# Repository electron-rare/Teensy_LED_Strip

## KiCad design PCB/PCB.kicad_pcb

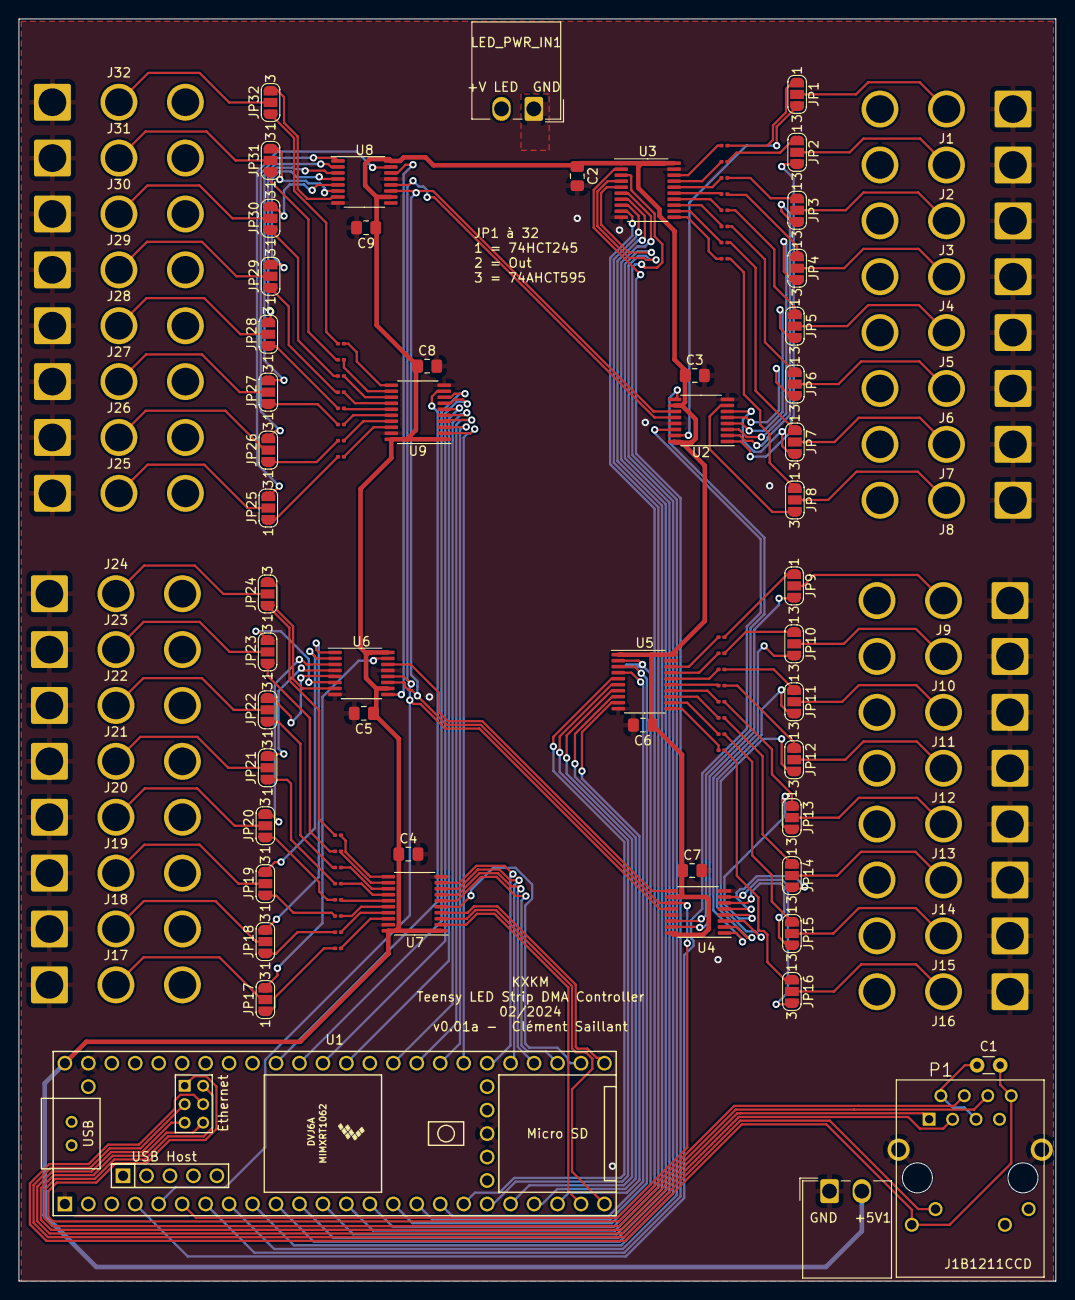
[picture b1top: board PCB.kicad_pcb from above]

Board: 2 copper layers, 112.3 x 136.7 mm, 117 parts (0 on the bottom side), 176 nets.

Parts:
+5V1: Screw_Terminal_01x02; Wago_734-162_1x02_P3.50mm_Horizontal
C1: 0.1uF; C_Disc_D3.0mm_W1.6mm_P2.50mm
C2, C3, C4, C5, C6, C7, C8, C9: 100nf; C_0805_2012Metric_Pad1.18x1.45mm_HandSolder
J1, J2, J3, J4, J5, J6, J7, J8, J9, J10, J11, J12, J13, J14, J15, J16, J17, J18, J19, J20, J21, J22, J23, J24, J25, J26, J27, J28, J29, J30, J31, J32: Conn_01x03_Pin; SolderWire-2.5sqmm_1x03_P7.2mm_D2.4mm_OD3.6mm
JP1, JP2, JP3, JP4, JP5, JP6, JP7, JP8, JP9, JP10, JP11, JP12, JP13, JP14, JP15, JP16, JP17, JP18, JP19, JP20, JP21, JP22, JP23, JP24, JP25, JP26, JP27, JP28, JP29, JP30, JP31, JP32: SolderJumper_3_Open; SolderJumper-3_P1.3mm_Open_RoundedPad1.0x1.5mm_NumberLabels
LED_PWR_IN1: Screw_Terminal_01x02; Wago_734-162_1x02_P3.50mm_Horizontal
P1: J1B1211CCD
R1, R2, R3, R4, R5, R6, R7, R8, R9, R10, R11, R12, R13, R14, R15, R16, R17, R18, R19, R20, R21, R22, R23, R24, R25, R26, R27, R28, R29, R30, R31, R32: 100R; R_0201_0603Metric
U1: Teensy4.1; Teensy41
U2, U4, U6, U8: 74AHCT595; TSSOP-16_4.4x5mm_P0.65mm
U3, U5, U7, U9: 74HCT245; TSSOP-20_4.4x6.5mm_P0.65mm

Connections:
+5V: +5V1.2, C2.1, C3.1, C4.1, C5.1, C6.1, C7.1, C8.1, C9.1, U1.48 (VIN), U2.10 (~SRCLR), U2.16 (VCC), U3.1 (A->B), U3.20 (VCC), U4.10 (~SRCLR), U4.16 (VCC), U5.1 (A->B), U5.20 (VCC), U6.10 (~SRCLR), U6.16 (VCC), U7.1 (A->B), U7.20 (VCC), U8.10 (~SRCLR), U8.16 (VCC), U9.1 (A->B), U9.20 (VCC)
+12V: J1.3, J2.3, J3.3, J4.3, J5.3, J6.3, J7.3, J8.3, J9.3, J10.3, J11.3, J12.3, J13.3, J14.3, J15.3, J16.3, J17.3, J18.3, J19.3, J20.3, J21.3, J22.3, J23.3, J24.3, J25.3, J26.3, J27.3, J28.3, J29.3, J30.3, J31.3, J32.3, LED_PWR_IN1.2
/LED_GPIO_1: U1.7 (5_IN2), U3.2 (A0)
/LED_GPIO_2: U1.8 (6_OUT1D), U3.3 (A1)
/LED_GPIO_3: U1.9 (7_RX2_OUT1A), U3.4 (A2)
/LED_GPIO_4: U1.10 (8_TX2_IN1), U3.5 (A3)
/LED_GPIO_5: U1.11 (9_OUT1C), U3.6 (A4)
/LED_GPIO_6: U1.12 (10_CS_MQSR), U3.7 (A5)
/LED_GPIO_7: U1.13 (11_MOSI_CTX1), U3.8 (A6)
/LED_GPIO_8: U1.14 (12_MISO_MQSL), U3.9 (A7)
/LED_GPIO_9: U1.15 (3V3), U5.2 (A0)
/LED_GPIO_10: U1.16 (24_A10_TX6_SCL2), U5.3 (A1)
/LED_GPIO_11: U1.17 (25_A11_RX6_SDA2), U5.4 (A2)
/LED_GPIO_12: U1.18 (26_A12_MOSI1), U5.5 (A3)
/LED_GPIO_13: U1.19 (27_A13_SCK1), U5.6 (A4)
/LED_GPIO_14: U1.20 (28_RX7), U5.7 (A5)
/LED_GPIO_15: U1.21 (29_TX7), U5.8 (A6)
/LED_GPIO_16: U1.22 (30_CRX3), U5.9 (A7)
/LED_GPIO_17: U1.23 (31_CTX3), U7.2 (A0)
/LED_GPIO_18: U1.24 (32_OUT1B), U7.3 (A1)
/LED_GPIO_19: U1.25 (33_MCLK2), U7.4 (A2)
/LED_GPIO_20: U1.26 (34_RX8), U7.5 (A3)
/LED_GPIO_21: U1.27 (35_TX8), U7.6 (A4)
/LED_GPIO_22: U1.28 (36_CS), U7.7 (A5)
/LED_GPIO_23: U1.29 (37_CS), U7.8 (A6)
/LED_GPIO_24: U1.30 (38_CS1_IN1), U7.9 (A7)
/LED_GPIO_25: U1.31 (39_MISO1_OUT1A), U9.2 (A0)
/LED_GPIO_26: U1.32 (40_A16), U9.3 (A1)
/LED_GPIO_27: U1.33 (41_A17), U9.4 (A2)
/LED_GPIO_28: U1.34 (GND), U9.5 (A3)
/LED_GPIO_29: U1.36 (14_A0_TX3_SPDIF_OUT), U9.6 (A4)
/LED_GPIO_30: U1.37 (15_A1_RX3_SPDIF_IN), U9.7 (A5)
/LED_GPIO_31: U1.38 (16_A2_RX4_SCL1), U9.8 (A6)
/LED_GPIO_32: U1.39 (17_A3_TX4_SDA1), U9.9 (A7)
/LED_R 1 to 8/LED_B_1: JP1.1 (A), R1.2
/LED_R 1 to 8/LED_B_2: JP2.1 (A), R2.2
/LED_R 1 to 8/LED_B_3: JP3.1 (A), R3.2
/LED_R 1 to 8/LED_B_4: JP4.1 (A), R4.2
/LED_R 1 to 8/LED_B_5: JP5.1 (A), R5.2
/LED_R 1 to 8/LED_B_6: JP6.1 (A), R6.2
/LED_R 1 to 8/LED_B_7: JP7.1 (A), R7.2
/LED_R 1 to 8/LED_B_8: JP8.1 (A), R8.2
/LED_R 1 to 8/LED_R_1: JP1.3 (B), U2.15 (QA)
/LED_R 1 to 8/LED_R_2: JP2.3 (B), U2.1 (QB)
/LED_R 1 to 8/LED_R_3: JP3.3 (B), U2.2 (QC)
/LED_R 1 to 8/LED_R_4: JP4.3 (B), U2.3 (QD)
/LED_R 1 to 8/LED_R_5: JP5.3 (B), U2.4 (QE)
/LED_R 1 to 8/LED_R_6: JP6.3 (B), U2.5 (QF)
/LED_R 1 to 8/LED_R_7: JP7.3 (B), U2.6 (QG)
/LED_R 1 to 8/LED_R_8: JP8.3 (B), U2.7 (QH)
/LED_R 1 to 8/SER_OUT: U2.9 (QH'), U4.14 (SER)
/LED_R 1 to 9/LED_B_1: JP9.1 (A), R9.2
/LED_R 1 to 9/LED_B_2: JP10.1 (A), R10.2
/LED_R 1 to 9/LED_B_3: JP11.1 (A), R11.2
/LED_R 1 to 9/LED_B_4: JP12.1 (A), R12.2
/LED_R 1 to 9/LED_B_5: JP13.1 (A), R13.2
/LED_R 1 to 9/LED_B_6: JP14.1 (A), R14.2
/LED_R 1 to 9/LED_B_7: JP15.1 (A), R15.2
/LED_R 1 to 9/LED_B_8: JP16.1 (A), R16.2
/LED_R 1 to 9/LED_R_1: JP9.3 (B), U4.15 (QA)
/LED_R 1 to 9/LED_R_2: JP10.3 (B), U4.1 (QB)
/LED_R 1 to 9/LED_R_3: JP11.3 (B), U4.2 (QC)
/LED_R 1 to 9/LED_R_4: JP12.3 (B), U4.3 (QD)
/LED_R 1 to 9/LED_R_5: JP13.3 (B), U4.4 (QE)
/LED_R 1 to 9/LED_R_6: JP14.3 (B), U4.5 (QF)
/LED_R 1 to 9/LED_R_7: JP15.3 (B), U4.6 (QG)
/LED_R 1 to 9/LED_R_8: JP16.3 (B), U4.7 (QH)
/LED_R 1 to 10/LED_B_1: JP25.1 (A), R25.2
/LED_R 1 to 10/LED_B_2: JP26.1 (A), R26.2
/LED_R 1 to 10/LED_B_3: JP27.1 (A), R27.2
/LED_R 1 to 10/LED_B_4: JP28.1 (A), R28.2
/LED_R 1 to 10/LED_B_5: JP29.1 (A), R29.2
/LED_R 1 to 10/LED_B_6: JP30.1 (A), R30.2
/LED_R 1 to 10/LED_B_7: JP31.1 (A), R31.2
/LED_R 1 to 10/LED_B_8: JP32.1 (A), R32.2
/LED_R 1 to 10/LED_R_1: JP25.3 (B), U8.15 (QA)
/LED_R 1 to 10/LED_R_2: JP26.3 (B), U8.1 (QB)
/LED_R 1 to 10/LED_R_3: JP27.3 (B), U8.2 (QC)
/LED_R 1 to 10/LED_R_4: JP28.3 (B), U8.3 (QD)
/LED_R 1 to 10/LED_R_5: JP29.3 (B), U8.4 (QE)
/LED_R 1 to 10/LED_R_6: JP30.3 (B), U8.5 (QF)
/LED_R 1 to 10/LED_R_7: JP31.3 (B), U8.6 (QG)
/LED_R 1 to 10/LED_R_8: JP32.3 (B), U8.7 (QH)
/LED_R 1 to 10/SER_IN: U6.9 (QH'), U8.14 (SER)
/LED_R 1 to 11/LED_B_1: JP17.1 (A), R17.2
/LED_R 1 to 11/LED_B_2: JP18.1 (A), R18.2
/LED_R 1 to 11/LED_B_3: JP19.1 (A), R19.2
/LED_R 1 to 11/LED_B_4: JP20.1 (A), R20.2
/LED_R 1 to 11/LED_B_5: JP21.1 (A), R21.2
/LED_R 1 to 11/LED_B_6: JP22.1 (A), R22.2
/LED_R 1 to 11/LED_B_7: JP23.1 (A), R23.2
/LED_R 1 to 11/LED_B_8: JP24.1 (A), R24.2
/LED_R 1 to 11/LED_R_1: JP17.3 (B), U6.15 (QA)
/LED_R 1 to 11/LED_R_2: JP18.3 (B), U6.1 (QB)
/LED_R 1 to 11/LED_R_3: JP19.3 (B), U6.2 (QC)
/LED_R 1 to 11/LED_R_4: JP20.3 (B), U6.3 (QD)
/LED_R 1 to 11/LED_R_5: JP21.3 (B), U6.4 (QE)
/LED_R 1 to 11/LED_R_6: JP22.3 (B), U6.5 (QF)
/LED_R 1 to 11/LED_R_7: JP23.3 (B), U6.6 (QG)
/LED_R 1 to 11/LED_R_8: JP24.3 (B), U6.7 (QH)
/LED_R 1 to 11/SER_IN: U4.9 (QH'), U6.14 (SER)
/RCLK: U1.5 (3_LRCLK2), U2.12 (RCLK), U4.12 (RCLK), U6.12 (RCLK), U8.12 (RCLK)
/SER_OUT: U1.6 (4_BCLK2), U2.11 (SRCLK), U4.11 (SRCLK), U6.11 (SRCLK), U8.11 (SRCLK)
/SRCLK: U1.4 (2_OUT2), U2.14 (SER)
GND: +5V1.1, C2.2, C3.2, C4.2, C5.2, C6.2, C7.2, C8.2, C9.2, J1.1, J2.1, J3.1, J4.1, J5.1, J6.1, J7.1, J8.1, J9.1, J10.1, J11.1, J12.1, J13.1, J14.1, J15.1, J16.1, J17.1, J18.1, J19.1, J20.1, J21.1, J22.1, J23.1, J24.1, J25.1, J26.1, J27.1, J28.1, J29.1, J30.1, J31.1, J32.1, LED_PWR_IN1.1, P1.13 (CH_GND@2), P1.14 (CH_GND@3), U1.1 (GND), U1.47 (GND), U1.52 (GND), U2.8 (GND), U2.13 (~OE), U3.10 (GND), U3.19 (CE), U4.8 (GND), U4.13 (~OE), U5.10 (GND), U5.19 (CE), U6.8 (GND), U6.13 (~OE), U7.10 (GND), U7.19 (CE), U8.8 (GND), U8.13 (~OE), U9.10 (GND), U9.19 (CE)
unnamed: J1.2, JP1.2 (C)
unnamed: J2.2, JP2.2 (C)
unnamed: J3.2, JP3.2 (C)
unnamed: J4.2, JP4.2 (C)
unnamed: J5.2, JP5.2 (C)
unnamed: J6.2, JP6.2 (C)
unnamed: J7.2, JP7.2 (C)
unnamed: J8.2, JP8.2 (C)
unnamed: J9.2, JP9.2 (C)
unnamed: J10.2, JP10.2 (C)
unnamed: J11.2, JP11.2 (C)
unnamed: J12.2, JP12.2 (C)
unnamed: J13.2, JP13.2 (C)
unnamed: J14.2, JP14.2 (C)
unnamed: J15.2, JP15.2 (C)
unnamed: J16.2, JP16.2 (C)
unnamed: J17.2, JP17.2 (C)
unnamed: J18.2, JP18.2 (C)
unnamed: J19.2, JP19.2 (C)
unnamed: J20.2, JP20.2 (C)
unnamed: J21.2, JP21.2 (C)
unnamed: J22.2, JP22.2 (C)
unnamed: J23.2, JP23.2 (C)
unnamed: J24.2, JP24.2 (C)
unnamed: J25.2, JP25.2 (C)
unnamed: J26.2, JP26.2 (C)
unnamed: J27.2, JP27.2 (C)
unnamed: J28.2, JP28.2 (C)
unnamed: J29.2, JP29.2 (C)
unnamed: J30.2, JP30.2 (C)
unnamed: J31.2, JP31.2 (C)
unnamed: J32.2, JP32.2 (C)
unnamed: C1.2, P1.8 (GH_GND@1), P1.9 (GRN-), U1.64 (GND)
unnamed: P1.10 (GRN+), U1.61 (LED)
unnamed: C1.1, P1.2 (TCT), P1.5 (RCT)
unnamed: P1.4 (RD+), U1.60 (R+)
unnamed: P1.6 (RD-), U1.65 (R-)
unnamed: P1.1 (TD+), U1.63 (T+)
unnamed: P1.3 (TD-), U1.62 (T-)
unnamed: R1.1, U3.18 (B0)
unnamed: R2.1, U3.17 (B1)
unnamed: R3.1, U3.16 (B2)
unnamed: R4.1, U3.15 (B3)
unnamed: R5.1, U3.14 (B4)
unnamed: R6.1, U3.13 (B5)
unnamed: R7.1, U3.12 (B6)
unnamed: R8.1, U3.11 (B7)
unnamed: R9.1, U5.18 (B0)
unnamed: R10.1, U5.17 (B1)
unnamed: R11.1, U5.16 (B2)
unnamed: R12.1, U5.15 (B3)
unnamed: R13.1, U5.14 (B4)
unnamed: R14.1, U5.13 (B5)
unnamed: R15.1, U5.12 (B6)
unnamed: R16.1, U5.11 (B7)
unnamed: R17.1, U7.18 (B0)
unnamed: R18.1, U7.17 (B1)
unnamed: R19.1, U7.16 (B2)
unnamed: R20.1, U7.15 (B3)
unnamed: R21.1, U7.14 (B4)
unnamed: R22.1, U7.13 (B5)
unnamed: R23.1, U7.12 (B6)
unnamed: R24.1, U7.11 (B7)
unnamed: R25.1, U9.18 (B0)
unnamed: R26.1, U9.17 (B1)
unnamed: R27.1, U9.16 (B2)
unnamed: R28.1, U9.15 (B3)
unnamed: R29.1, U9.14 (B4)
unnamed: R30.1, U9.13 (B5)
unnamed: R31.1, U9.12 (B6)
unnamed: R32.1, U9.11 (B7)

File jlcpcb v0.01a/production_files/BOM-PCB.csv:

Comment,Designator,Footprint,LCSC
100nf,"C2,C3,C4,C5,C6,C7,C8,C9",C_0805_2012Metric_Pad1.18x1.45mm_HandSolder,C14663
100R,"R1,R10,R11,R12,R13,R14,R15,R16,R17,R18,R19,R2,R20,R21,R22,R23,R24,R25,R26,R27,R28,R29,R3,R30,R31,R32,R4,R5,R6,R7,R8,R9",R_0201_0603Metric,C22775
74AHCT595,"U2,U4,U6,U8",TSSOP-16_4.4x5mm_P0.65mm,C460504
74HCT245,"U3,U5,U7,U9",TSSOP-20_4.4x6.5mm_P0.65mm,C6779
J1B1211CCD,P1,J1B1211CCD,C910371
0.1uF,C1,C_Disc_D3.0mm_W1.6mm_P2.50mm,
Teensy4.1,U1,Teensy41,
Screw_Terminal_01x02,LED_PWR_IN1,Wago_734-162_1x02_P3.50mm_Horizontal,

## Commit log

2024-02-22 initial release
    initial release
2024-02-22 add 3D view
2024-02-22 add jlcpcb production file
